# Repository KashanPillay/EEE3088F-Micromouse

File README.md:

# EEE3088F-Micromouse
A repository to manage and control versions pertaining to the EEE3088F Micro-mouse Project and all sub-projects.
This GitHub contains 2 folders, each carrying relevant information regarding a specific subsystem: the first is Sensing and the second is Power. There are multiple folders within each subsystem folder. There is one containing all the datasheets for components selected for the final designs. These folders are labeled "Data sheets". In addition, there is a folder titled 'Interim Design Report' in each subsystem which contains the completed Interim Design Report. Lastly, all Gerber files and Bill Of Materials files can be found in the last folder. Thank you for visiting the GitHub :)

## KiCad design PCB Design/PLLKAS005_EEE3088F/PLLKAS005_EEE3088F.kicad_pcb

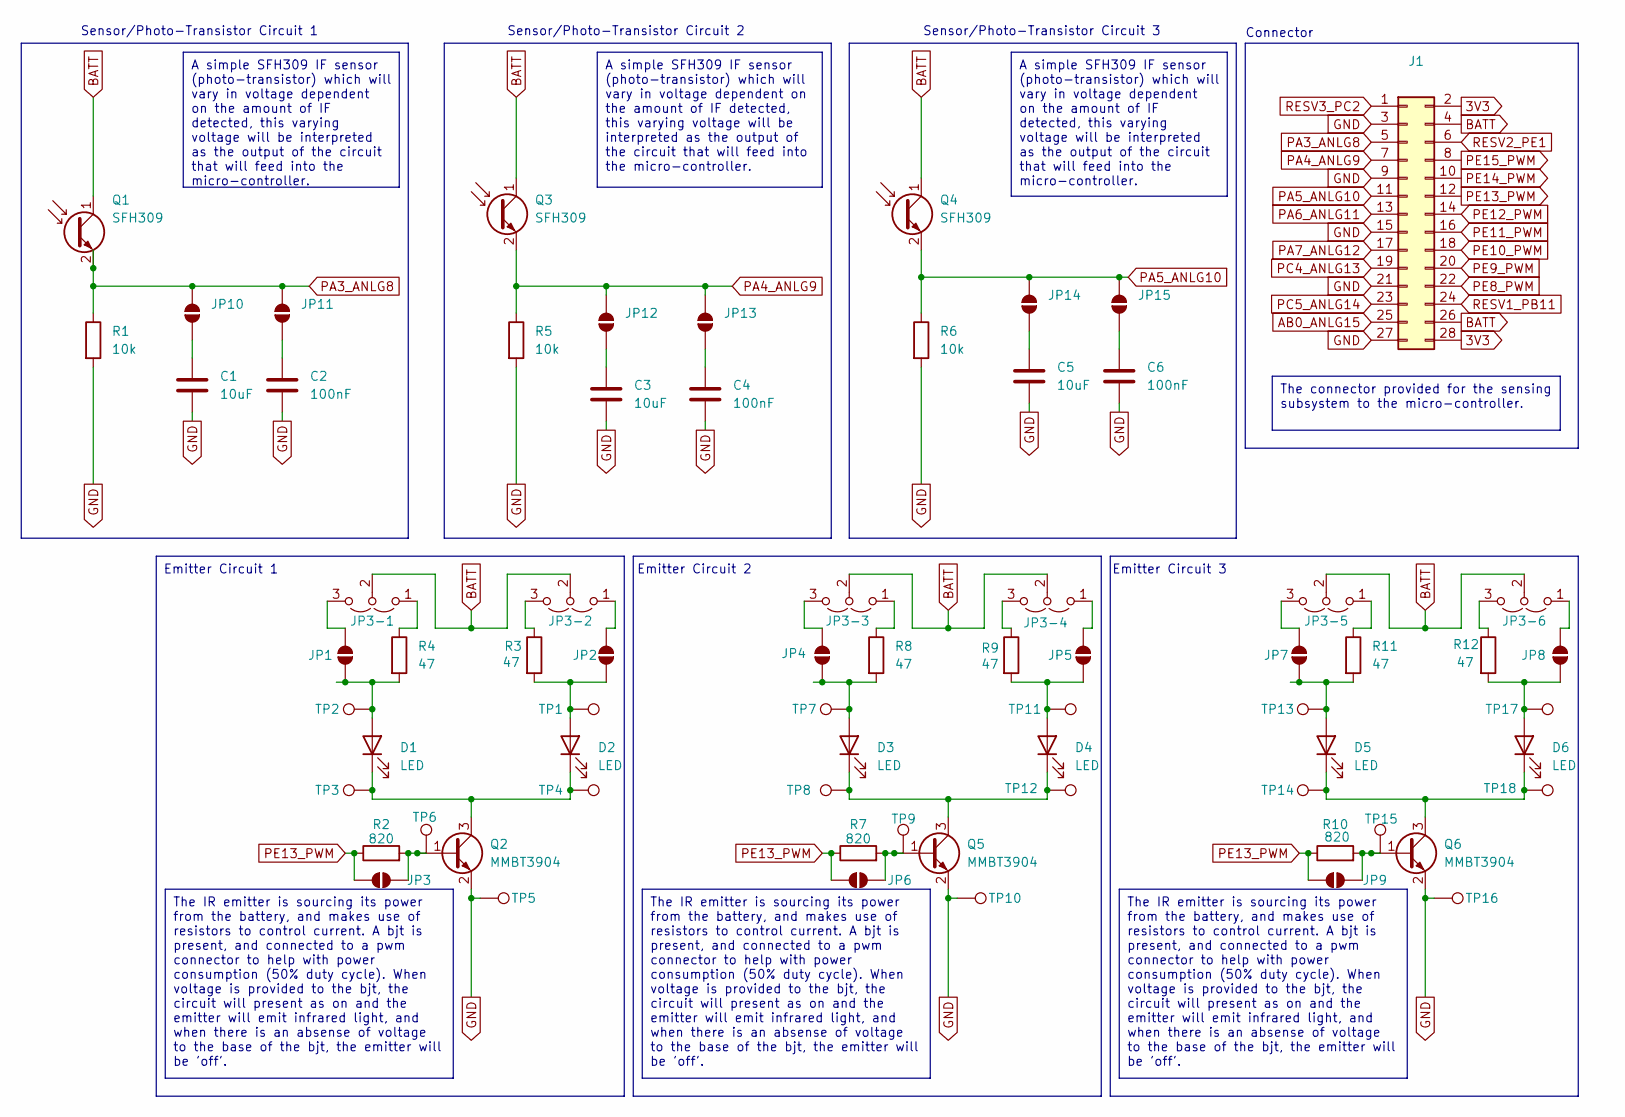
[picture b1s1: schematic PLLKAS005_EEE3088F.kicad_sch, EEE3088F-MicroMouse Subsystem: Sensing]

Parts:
C1, C3, C5: 10uF; C_0603_1608Metric
C2, C4, C6: 100nF; C_0603_1608Metric
D1, D2, D3, D4, D5, D6: LED; LED_D5.0mm_Horizontal_O1.27mm_Z3.0mm_IRBlack
J1: Conn_02x14_Odd_Even; PinHeader_2x14_P2.54mm_Vertical
JP1, JP2, JP3, JP4, JP5, JP6, JP7, JP8, JP9, JP10, JP11, JP12, JP13, JP14, JP15: SolderJumper_2_Open; SolderJumper-2_P1.3mm_Open_Pad1.0x1.5mm
JP3-1, JP3-2, JP3-3, JP3-4, JP3-5, JP3-6: Jumper_3_Open; SolderJumper-3_P1.3mm_Open_Pad1.0x1.5mm
Q1, Q3, Q4: SFH309; LED_D3.0mm_Horizontal_O1.27mm_Z2.0mm_Clear
Q2, Q5, Q6: MMBT3904; SOT-23
R1, R5, R6: 10k; R_0603_1608Metric
R2, R7, R10: 820; R_0603_1608Metric
R3, R4, R8, R9, R11, R12: 47; R_0603_1608Metric
TP1, TP2, TP3, TP4, TP5, TP6, TP7, TP8, TP9, TP10, TP11, TP12, TP13, TP14, TP15, TP16, TP17, TP18: TestPoint; TestPoint_Pad_D3.0mm

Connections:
3V3: J1.2, J1.28
AB0: J1.25
BATT: J1.4, J1.26, JP3-1.2 (C), JP3-2.2 (C), JP3-3.2 (C), JP3-4.2 (C), JP3-5.2 (C), JP3-6.2 (C), Q1.1 (C), Q3.1 (C), Q4.1 (C)
GND: C1.2, C2.2, C3.2, C4.2, C5.2, C6.2, J1.3, J1.9, J1.15, J1.21, J1.27, Q2.2 (E), Q5.2 (E), Q6.2 (E), R1.2, R5.2, R6.2, TP5.1, TP10.1, TP16.1
unnamed: D1.2 (A), JP1.1 (A), R4.2, TP2.1
unnamed: D1.1 (K), D2.1 (K), Q2.3 (C), TP3.1, TP4.1
unnamed: D2.2 (A), JP2.1 (A), R3.2, TP1.1
unnamed: D3.2 (A), JP4.1 (A), R8.2, TP7.1
unnamed: D3.1 (K), D4.1 (K), Q5.3 (C), TP8.1, TP12.1
unnamed: D4.2 (A), JP5.1 (A), R9.2, TP11.1
unnamed: D5.2 (A), JP7.1 (A), R11.2, TP13.1
unnamed: D5.1 (K), D6.1 (K), Q6.3 (C), TP14.1, TP18.1
unnamed: D6.2 (A), JP8.1 (A), R12.2, TP17.1
unnamed: JP1.2 (B), JP3-1.3 (B)
unnamed: JP2.2 (B), JP3-2.1 (A)
unnamed: JP3-1.1 (A), R4.1
unnamed: JP3-2.3 (B), R3.1
unnamed: JP3-3.1 (A), R8.1
unnamed: JP3-3.3 (B), JP4.2 (B)
unnamed: JP3-4.1 (A), JP5.2 (B)
unnamed: JP3-4.3 (B), R9.1
unnamed: JP3-5.1 (A), R11.1
unnamed: JP3-5.3 (B), JP7.2 (B)
unnamed: JP3-6.1 (A), JP8.2 (B)
unnamed: JP3-6.3 (B), R12.1
unnamed: JP3.1 (A), Q2.1 (B), R2.2, TP6.1
unnamed: JP6.1 (A), Q5.1 (B), R7.2, TP9.1
unnamed: JP9.1 (A), Q6.1 (B), R10.2, TP15.1
unnamed: C1.1, JP10.1 (A)
unnamed: C2.1, JP11.1 (A)
unnamed: C3.1, JP12.1 (A)
unnamed: C4.1, JP13.1 (A)
unnamed: C5.1, JP14.1 (A)
unnamed: C6.1, JP15.1 (A)
PA3: J1.5, JP10.2 (B), JP11.2 (B), Q1.2 (E), R1.1
PA4: J1.7, JP12.2 (B), JP13.2 (B), Q3.2 (E), R5.1
PA5: J1.11, JP14.2 (B), JP15.2 (B), Q4.2 (E), R6.1
PA6: J1.13
PA7: J1.17
PC4: J1.19
PC5: J1.23
PE8: J1.22
PE9: J1.20
PE10: J1.18
PE11: J1.16
PE12: J1.14
PE13: J1.12, JP3.2 (B), JP6.2 (B), JP9.2 (B), R2.1, R7.1, R10.1
PE14: J1.10
PE15: J1.8
RESV1: J1.24
RESV2: J1.6
RESV3: J1.1

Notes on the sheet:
The IR emitter is sourcing its power from the battery, and makes use of resistors to control current. A bjt is present, and connected to a pwm connector to help with power consumption (50% duty cycle). When voltage is provided to the bjt, the circuit will present as on and the emitter will emit inf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
A simple SFH309 IF sensor (photo-transistor) which will vary in voltage dependent on the amount of IF detected, this varying voltage will be interpreted as the output of the circuit that will feed into the micro-controller.
The connector provided for the sensing subsystem to the micro-controller.
Sensor/Photo-Transistor Circuit 2
Emitter Circuit 3
Sensor/Photo-Transistor Circuit 1
Sensor/Photo-Transistor Circuit 3
Connector
Emitter Circuit 1
Emitter Circuit 2

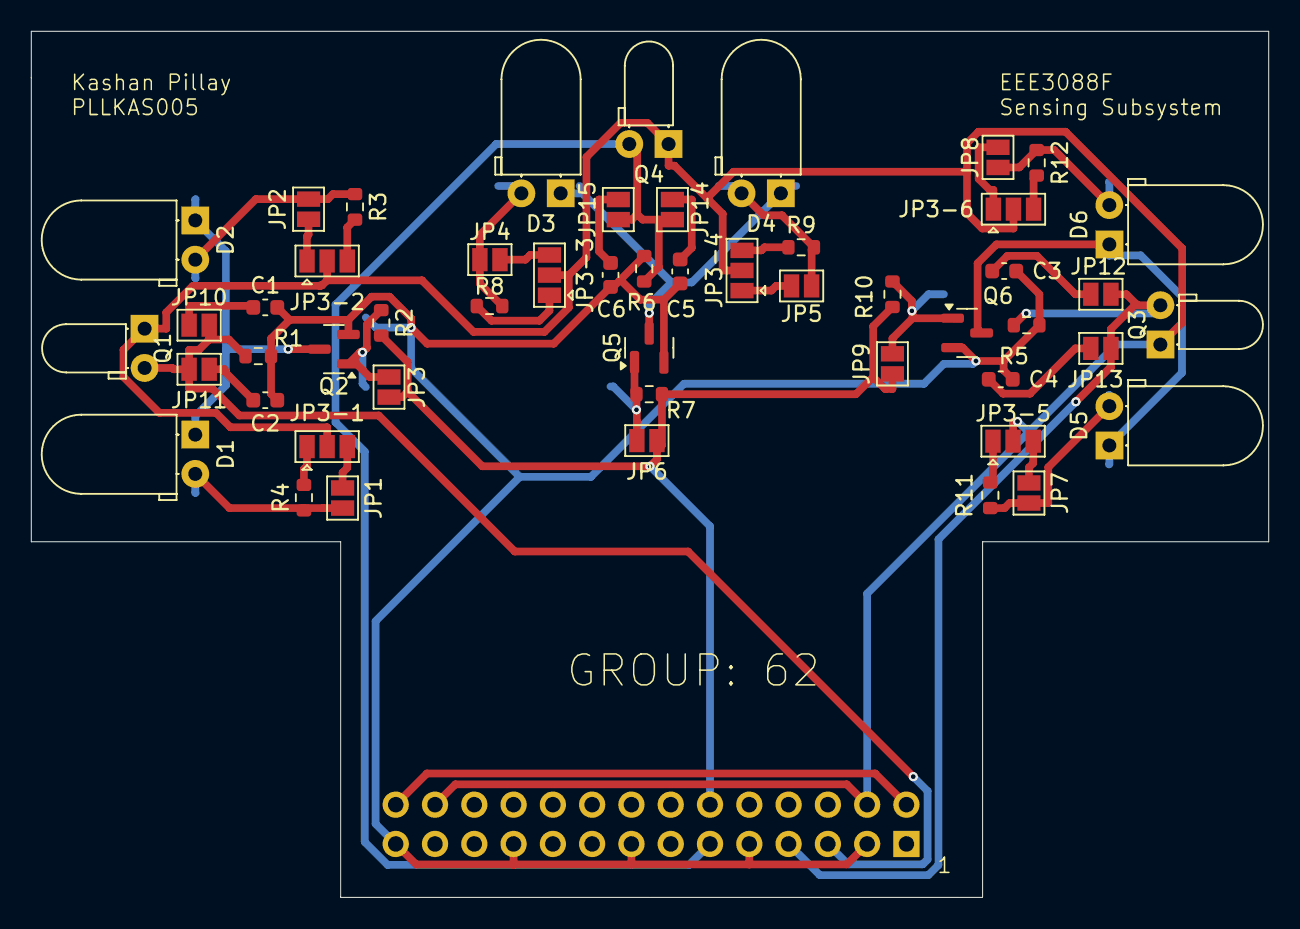
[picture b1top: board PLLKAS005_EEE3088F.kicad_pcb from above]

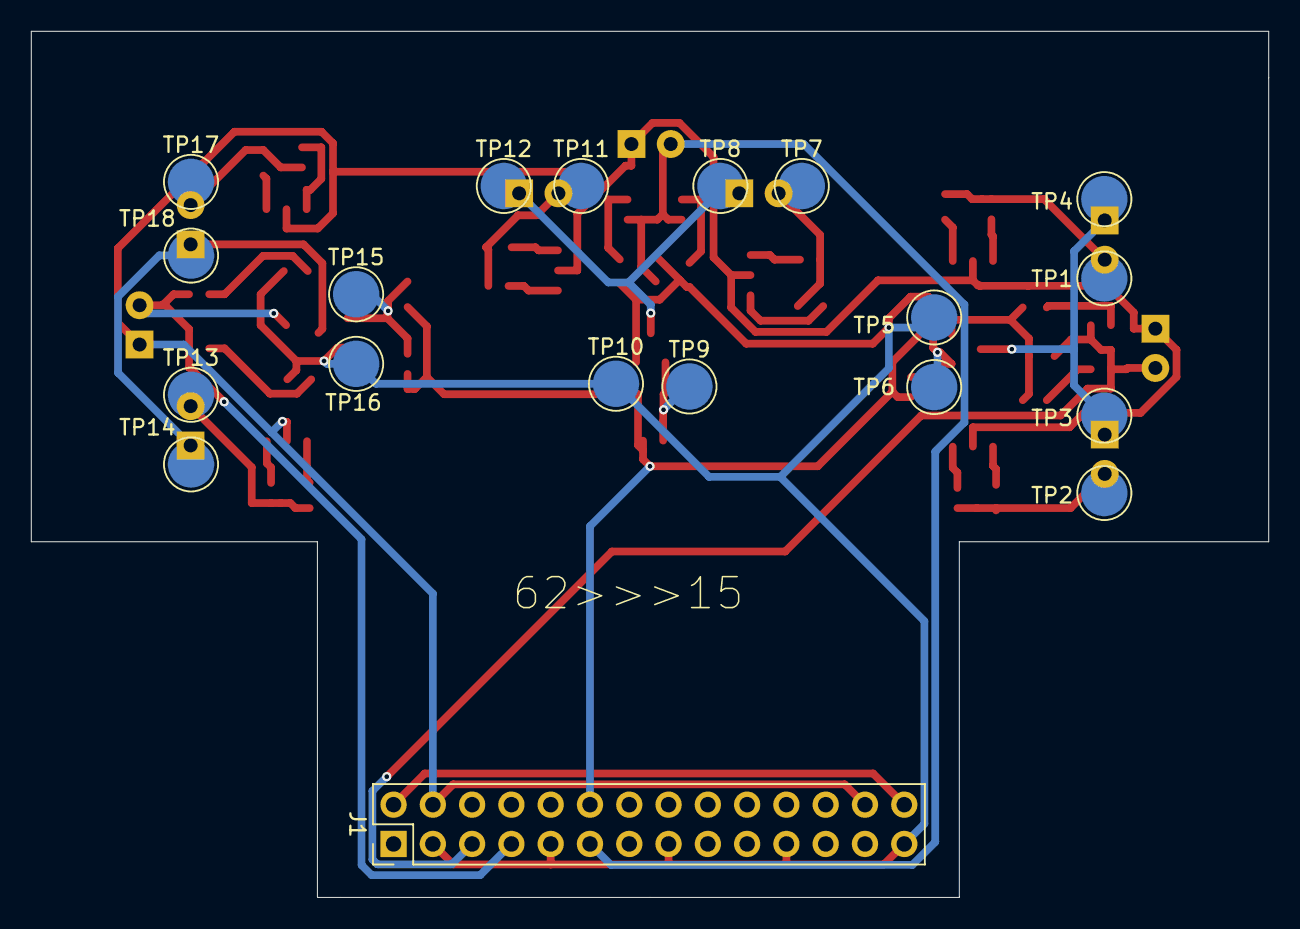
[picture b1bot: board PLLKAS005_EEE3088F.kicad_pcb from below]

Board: 2 copper layers, 80.0 x 56.0 mm, 70 parts (19 on the bottom side), 37 nets.

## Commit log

2024-03-18 Basic KiCAD assistance page.
2024-03-18 KiCAD_Basics
2024-03-18 Initial Commit for Project Description Page
    Version 4
2024-03-20 Version 5 of Project Doc
2024-03-20 V5 Project Doc
2024-03-20 Motor Driver IC: Possible datasheet
    $0.894 and over 2000 stock
    Needs 5 capacitors and 3 resistors (estimate)
2024-03-22 IC for charging circuit
2024-03-22 RESISTOR: 10K datasheet
2024-04-19 Add files via upload
    new version of project document
2024-04-21 DataSheets for final selected components
2024-04-21 Interim Report Figures
2024-04-21 Gerber file submission
2024-04-21 Completed interim report
2024-04-21 Addition of Datasheets.
2024-04-21 Addition of KiCad PCB Files and Interim Report Files
2024-04-21 The power subsystem information
2024-04-21 restructure
